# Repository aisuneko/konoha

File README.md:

# Project "konoha"

4-port pure Type-C USB3.0 hub, based on WCH CH634X.

We have:
- All 4 ports in Type-C
- max. approx. USB3.2Gen1 transfer rate (~500MB/s); compatible with USB2.0
- Dedicated charging port
- Adequate ESD protection
- A symmetrical look
- One-sided components for ease of assembly

Name is inspired by Akisato Konoha from *16-bit Sensation*.

## Schematic

Aside from my original idea of forcefully converting the three USB-A downstream ports provided by the CH634X to Type-C, it is largely based on CH634X's reference design with modifications.

Datasheets of the most important chips used in this design could be found under [docs](./docs/).

TL;DR: The USB-A to C conversion is done with TI's HD3SS3220 analog muxes (which appears to be as costly as the CH634X controller itself). CH217 is used for OVC protection while the CH213 diode realize the isolation between 5V and 5VD. ESD protection is realized by the TPD4E02B04 array (USBSS) and USBLC6-2SC6 (USBFS).

## Board

See the board in action:

The board is fabricated using JLCPCB's default JLC04161H-3313 stackup so it should be fairly easy to order your own. Feel free to share any feedback and suggestions on the board design and component routing as I'm also new to high-speed PCB design.

## Caveats

- The board is rather unstable with multiple devices transferring data simultaneously. Certain ports might trigger an occassional hub reset with `disabled by hub (EMI?), re-enabling...` in dmesg.

  Will try to fix in the next revision by improving EMI at the shields of the Type-C connectors, as well as revising the power supply circuit to ensure it's sufficient.

- BOM costs are a bit high; I'll see if I can switch to a cheaper analog mux to reduce costs (and perhaps component count).

## Changelog

- rev1 (2025/11/28): first failed prototype. I can't get it soldered properly in the first place
- rev2 (2026/05/12): Initial working release

## License

As no firmware is involved in this project, it's under `CERN-OHL-S-2.0`.

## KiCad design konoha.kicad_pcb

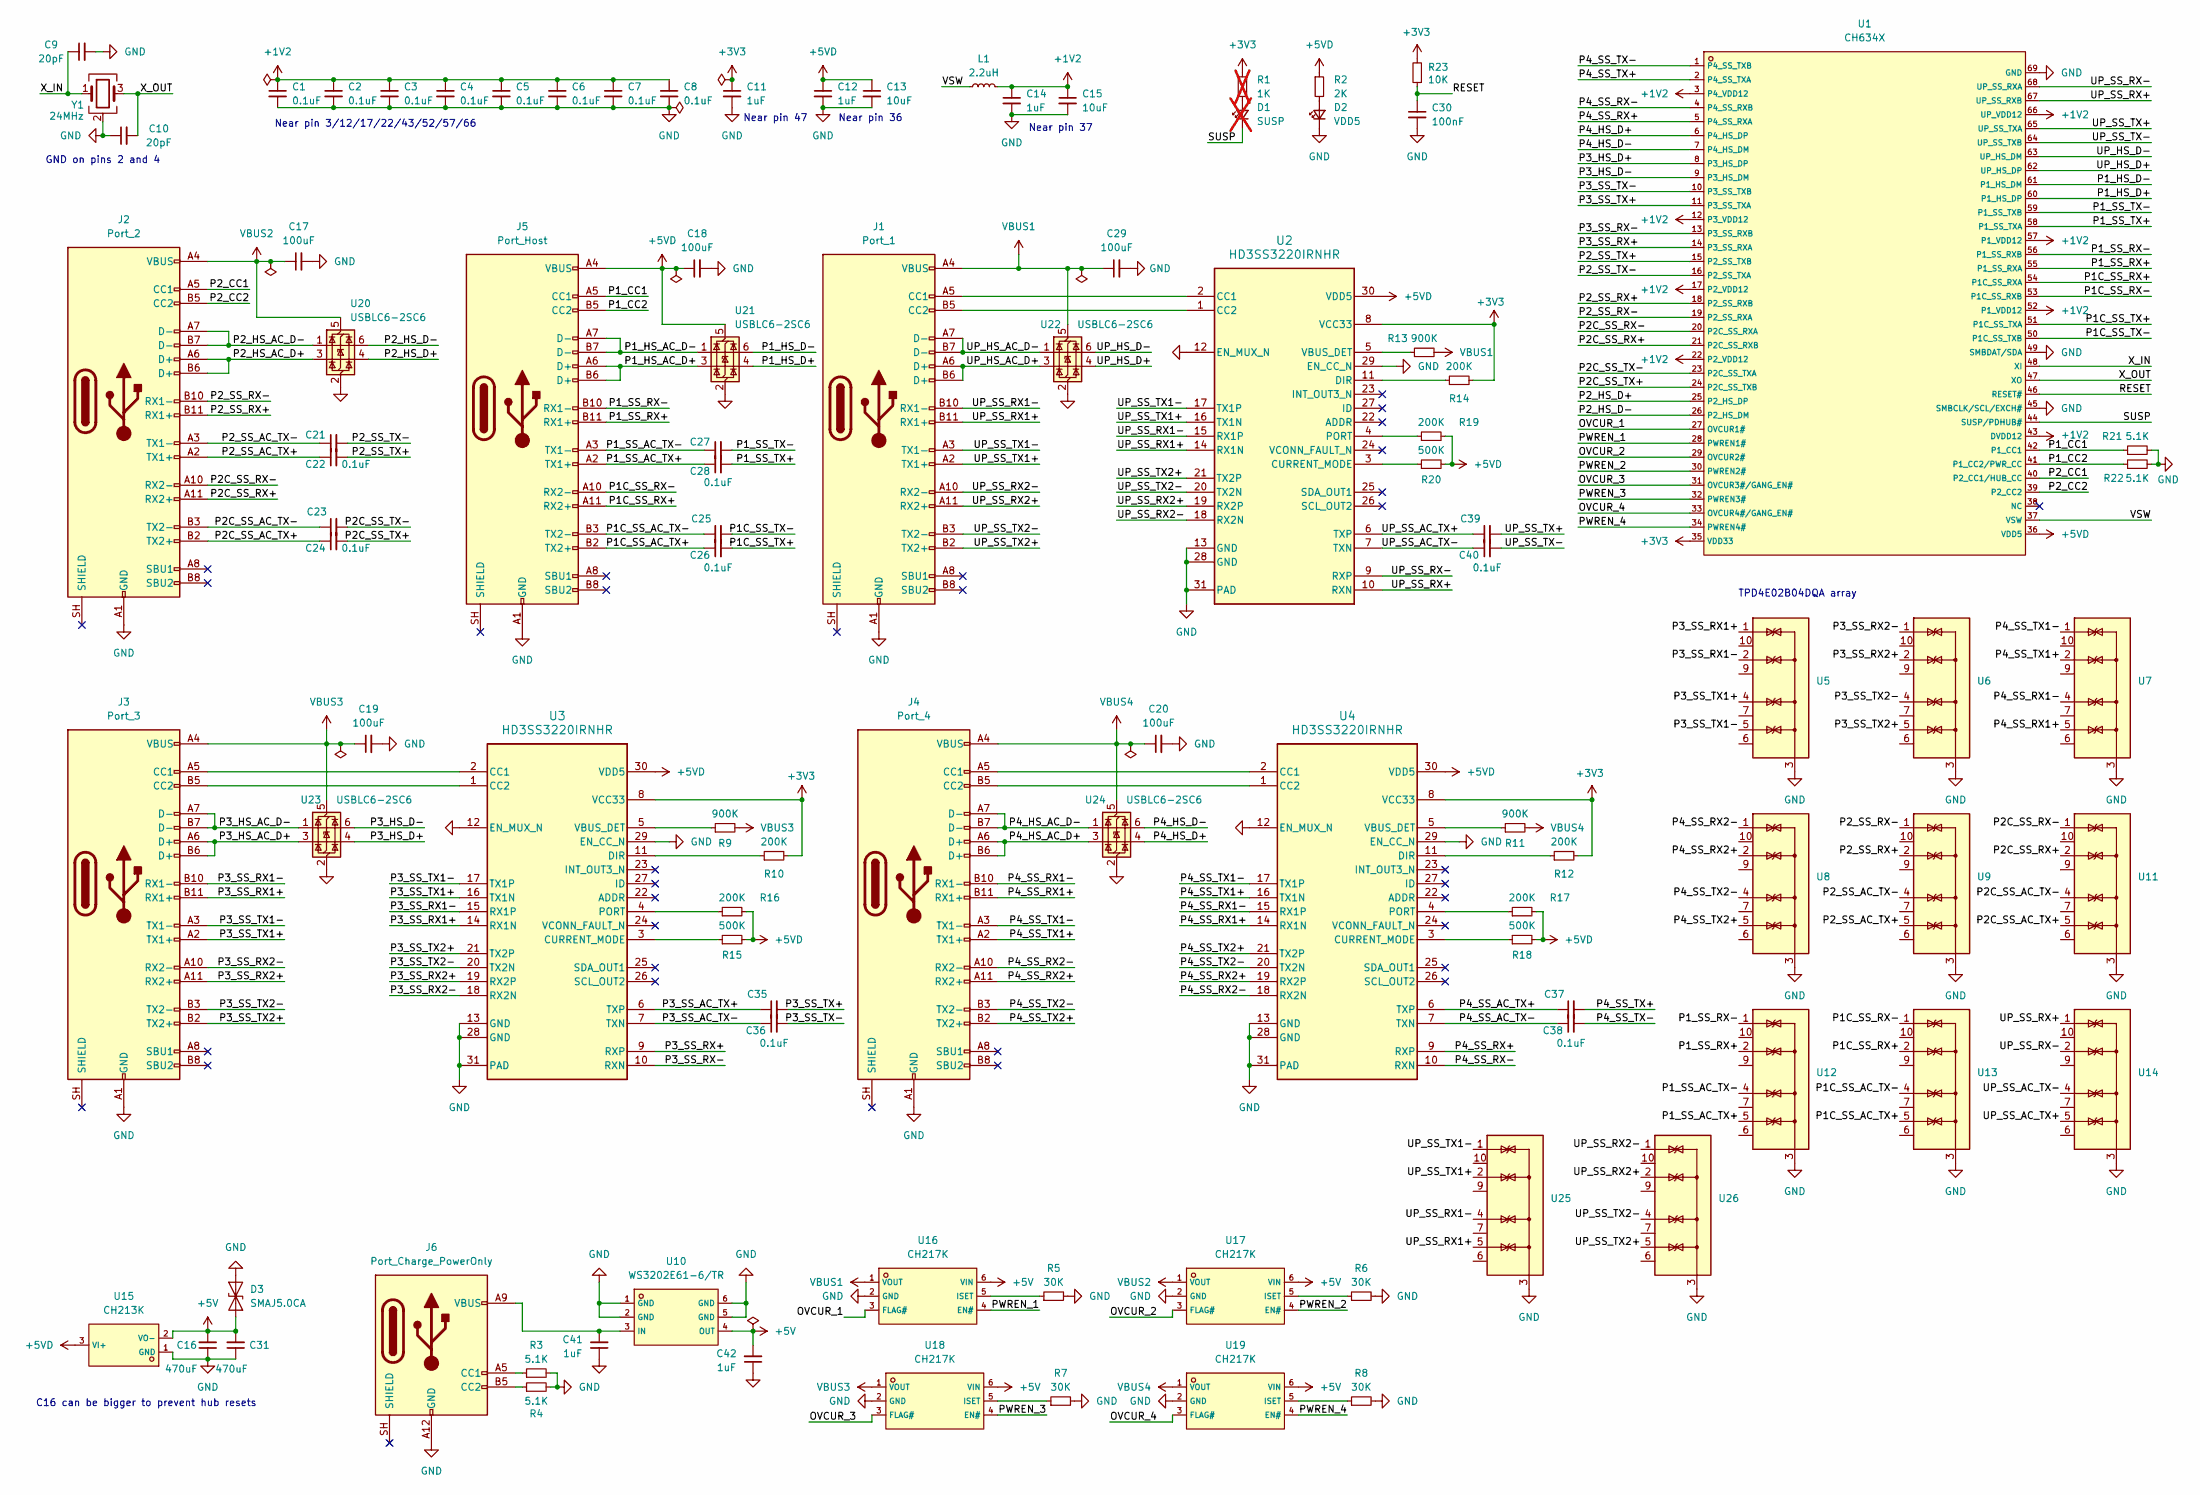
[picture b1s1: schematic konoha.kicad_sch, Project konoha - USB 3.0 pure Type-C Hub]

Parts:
C1, C2, C3, C4, C5, C6, C7, C8, C21, C22, C23, C24, C25, C26, C27, C28, C35, C36, C37, C38, C39, C40: 0.1uF; C_0603_1608Metric_Pad1.08x0.95mm_HandSolder
C9, C10: 20pF; C_0603_1608Metric_Pad1.08x0.95mm_HandSolder
C11, C12, C14, C41, C42: 1uF; C_0603_1608Metric_Pad1.08x0.95mm_HandSolder
C13, C15: 10uF; C_0603_1608Metric_Pad1.08x0.95mm_HandSolder
C16, C31: 470uF; CP_Elec_6.3x7.7
C17, C18, C19, C20, C29: 100uF; C_1206_3216Metric
C30: 100nF; C_0603_1608Metric_Pad1.08x0.95mm_HandSolder
D1: SUSP; LED_0805_2012Metric; not fitted
D2: VDD5; LED_0805_2012Metric
D3: SMAJ5.0CA; D_SMA
J1: Port_1; TYPE-C-USB-SMD_QCHT-143
J2: Port_2; TYPE-C-USB-SMD_QCHT-143
J3: Port_3; TYPE-C-USB-SMD_QCHT-143
J4: Port_4; TYPE-C-USB-SMD_QCHT-143
J5: Port_Host; TYPE-C-USB-SMD_QCHT-143
J6: Port_Charge_PowerOnly; USB_C_Receptacle_HRO_TYPE-C-31-M-17
L1: 2.2uH; L_0805_2012Metric_Pad1.05x1.20mm_HandSolder
R1: 1K; R_0603_1608Metric_Pad0.98x0.95mm_HandSolder; not fitted
R2: 2K; R_0603_1608Metric_Pad0.98x0.95mm_HandSolder
R3, R4, R21, R22: 5.1K; R_0603_1608Metric_Pad0.98x0.95mm_HandSolder
R5, R6, R7, R8: 30K; R_0603_1608Metric_Pad0.98x0.95mm_HandSolder
R9, R11, R13: 900K; R_0603_1608Metric_Pad0.98x0.95mm_HandSolder
R10, R12, R14, R16, R17, R19: 200K; R_0603_1608Metric_Pad0.98x0.95mm_HandSolder
R15, R18, R20: 500K; R_0603_1608Metric_Pad0.98x0.95mm_HandSolder
R23: 10K; R_0603_1608Metric_Pad0.98x0.95mm_HandSolder
U1: CH634X; QFN-68_L8.0-W8.0-P0.40-BL-EP6.2; LCSC C48985831
U2, U3, U4: HD3SS3220IRNHR; Texas_RNH0030A_WQFN-30-1EP_2.5x4.5mm_P0.4mm_EP1.2x3.2mm_The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
U5, U6, U7, U8, U9, U11, U12, U13, U14, U25, U26: TPD4E02B04DQA; USON-10_2.5x1.0mm_P0.5mm
U10: WS3202E61-6/TR; SOT-23-6_L2.9-W1.6-P0.95-LS2.8-BR; LCSC C191359
U15: CH213K; SOT-23-3_L2.9-W1.6-P1.90-LS2.8-BR; LCSC C5456874
U16, U17, U18, U19: CH217K; SOT-23-6_L2.9-W1.6-P0.95-LS2.8-BL; LCSC C7462749
U20, U21, U22, U23, U24: USBLC6-2SC6; SOT-23-6
Y1: 24MHz; Crystal_SMD_2016-4Pin_2.0x1.6mm

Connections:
+1V2: C1.1, C2.1, C3.1, C4.1, C5.1, C6.1, C7.1, C8.1, C14.1, C15.1, L1.2, U1.3 (P4_VDD12), U1.12 (P3_VDD12), U1.17 (P2_VDD12), U1.22 (P2_VDD12), U1.43 (DVDD12), U1.52 (P1_VDD12), U1.57 (P1_VDD12), U1.66 (UP_VDD12)
+3V3: C11.1, R1.1, R10.2, R12.2, R14.2, R23.2, U1.35 (VDD33), U2.8 (VCC33), U3.8 (VCC33), U4.8 (VCC33)
+5V: C16.2, C31.2, C42.2, D3.1 (A1), U10.4 (OUT), U15.2 (VO-), U16.6 (VIN), U17.6 (VIN), U18.6 (VIN), U19.6 (VIN)
+5VD: C12.1, C13.1, C18.1, J5.A4 (VBUS), J5.A9 (VBUS), J5.B4 (VBUS), J5.B9 (VBUS), R2.1, R15.2, R16.2, R17.2, R18.2, R19.2, R20.2, U1.36 (VDD5), U2.30 (VDD5), U3.30 (VDD5), U4.30 (VDD5), U15.3 (VI+), U21.5 (VBUS)
/OVCUR_1: U1.27 (OVCUR1#), U16.3 (FLAG#)
/OVCUR_2: U1.29 (OVCUR2#), U17.3 (FLAG#)
/OVCUR_3: U1.31 (OVCUR3#/GANG_EN#), U18.3 (FLAG#)
/OVCUR_4: U1.33 (OVCUR4#/GANG_EN#), U19.3 (FLAG#)
/P1C_SS_AC_TX+: C26.1, J5.B2 (TX2+), U13.5 (IO4)
/P1C_SS_AC_TX-: C25.1, J5.B3 (TX2-), U13.4 (IO3)
/P1C_SS_RX+: J5.A11 (RX2+), U1.54 (P1C_SS_RXA), U13.2 (IO2)
/P1C_SS_RX-: J5.A10 (RX2-), U1.53 (P1C_SS_RXB), U13.1 (IO1)
/P1C_SS_TX+: C26.2, U1.51 (P1C_SS_TXA)
/P1C_SS_TX-: C25.2, U1.50 (P1C_SS_TXB)
/P1_CC1: J5.A5 (CC1), R21.1, U1.42 (P1_CC1)
/P1_CC2: J5.B5 (CC2), R22.1, U1.41 (P1_CC2/PWR_CC)
/P1_HS_AC_D+: J5.A6 (D+), J5.B6 (D+), U21.3 (I/O2)
/P1_HS_AC_D-: J5.A7 (D-), J5.B7 (D-), U21.1 (I/O1)
/P1_HS_D+: U1.60 (P1_HS_DP), U21.4 (I/O2)
/P1_HS_D-: U1.61 (P1_HS_DM), U21.6 (I/O1)
/P1_SS_AC_TX+: C28.1, J5.A2 (TX1+), U12.5 (IO4)
/P1_SS_AC_TX-: C27.1, J5.A3 (TX1-), U12.4 (IO3)
/P1_SS_RX+: J5.B11 (RX1+), U1.55 (P1_SS_RXA), U12.2 (IO2)
/P1_SS_RX-: J5.B10 (RX1-), U1.56 (P1_SS_RXB), U12.1 (IO1)
/P1_SS_TX+: C28.2, U1.58 (P1_SS_TXA)
/P1_SS_TX-: C27.2, U1.59 (P1_SS_TXB)
/P2C_SS_AC_TX+: C24.1, J2.B2 (TX2+), U11.5 (IO4)
/P2C_SS_AC_TX-: C23.1, J2.B3 (TX2-), U11.4 (IO3)
/P2C_SS_RX+: J2.A11 (RX2+), U1.21 (P2C_SS_RXB), U11.2 (IO2)
/P2C_SS_RX-: J2.A10 (RX2-), U1.20 (P2C_SS_RXA), U11.1 (IO1)
/P2C_SS_TX+: C24.2, U1.24 (P2C_SS_TXB)
/P2C_SS_TX-: C23.2, U1.23 (P2C_SS_TXA)
/P2_CC1: J2.A5 (CC1), U1.40 (P2_CC1/HUB_CC)
/P2_CC2: J2.B5 (CC2), U1.39 (P2_CC2)
/P2_HS_AC_D+: J2.A6 (D+), J2.B6 (D+), U20.3 (I/O2)
/P2_HS_AC_D-: J2.A7 (D-), J2.B7 (D-), U20.1 (I/O1)
/P2_HS_D+: U1.25 (P2_HS_DP), U20.4 (I/O2)
/P2_HS_D-: U1.26 (P2_HS_DM), U20.6 (I/O1)
/P2_SS_AC_TX+: C22.1, J2.A2 (TX1+), U9.5 (IO4)
/P2_SS_AC_TX-: C21.1, J2.A3 (TX1-), U9.4 (IO3)
/P2_SS_RX+: J2.B11 (RX1+), U1.18 (P2_SS_RXB), U9.2 (IO2)
/P2_SS_RX-: J2.B10 (RX1-), U1.19 (P2_SS_RXA), U9.1 (IO1)
/P2_SS_TX+: C22.2, U1.15 (P2_SS_TXB)
/P2_SS_TX-: C21.2, U1.16 (P2_SS_TXA)
/P3_HS_AC_D+: J3.A6 (D+), J3.B6 (D+), U23.3 (I/O2)
/P3_HS_AC_D-: J3.A7 (D-), J3.B7 (D-), U23.1 (I/O1)
/P3_HS_D+: U1.8 (P3_HS_DP), U23.4 (I/O2)
/P3_HS_D-: U1.9 (P3_HS_DM), U23.6 (I/O1)
/P3_SS_AC_TX+: C35.1, U3.6 (TXP)
/P3_SS_AC_TX-: C36.1, U3.7 (TXN)
/P3_SS_RX1+: J3.B11 (RX1+), U3.14 (RX1N), U5.1 (IO1)
/P3_SS_RX1-: J3.B10 (RX1-), U3.15 (RX1P), U5.2 (IO2)
/P3_SS_RX2+: J3.A11 (RX2+), U3.19 (RX2P), U6.2 (IO2)
/P3_SS_RX2-: J3.A10 (RX2-), U3.18 (RX2N), U6.1 (IO1)
/P3_SS_RX+: U1.14 (P3_SS_RXA), U3.9 (RXP)
/P3_SS_RX-: U1.13 (P3_SS_RXB), U3.10 (RXN)
/P3_SS_TX1+: J3.A2 (TX1+), U3.16 (TX1N), U5.4 (IO3)
/P3_SS_TX1-: J3.A3 (TX1-), U3.17 (TX1P), U5.5 (IO4)
/P3_SS_TX2+: J3.B2 (TX2+), U3.21 (TX2P), U6.5 (IO4)
/P3_SS_TX2-: J3.B3 (TX2-), U3.20 (TX2N), U6.4 (IO3)
/P3_SS_TX+: C35.2, U1.11 (P3_SS_TXA)
/P3_SS_TX-: C36.2, U1.10 (P3_SS_TXB)
/P4_HS_AC_D+: J4.A6 (D+), J4.B6 (D+), U24.3 (I/O2)
/P4_HS_AC_D-: J4.A7 (D-), J4.B7 (D-), U24.1 (I/O1)
/P4_HS_D+: U1.6 (P4_HS_DP), U24.4 (I/O2)
/P4_HS_D-: U1.7 (P4_HS_DM), U24.6 (I/O1)
/P4_SS_AC_TX+: C37.1, U4.6 (TXP)
/P4_SS_AC_TX-: C38.1, U4.7 (TXN)
/P4_SS_RX1+: J4.B11 (RX1+), U4.14 (RX1N), U7.5 (IO4)
/P4_SS_RX1-: J4.B10 (RX1-), U4.15 (RX1P), U7.4 (IO3)
/P4_SS_RX2+: J4.A11 (RX2+), U4.19 (RX2P), U8.2 (IO2)
/P4_SS_RX2-: J4.A10 (RX2-), U4.18 (RX2N), U8.1 (IO1)
/P4_SS_RX+: U1.5 (P4_SS_RXA), U4.9 (RXP)
/P4_SS_RX-: U1.4 (P4_SS_RXB), U4.10 (RXN)
/P4_SS_TX1+: J4.A2 (TX1+), U4.16 (TX1N), U7.2 (IO2)
/P4_SS_TX1-: J4.A3 (TX1-), U4.17 (TX1P), U7.1 (IO1)
/P4_SS_TX2+: J4.B2 (TX2+), U4.21 (TX2P), U8.5 (IO4)
/P4_SS_TX2-: J4.B3 (TX2-), U4.20 (TX2N), U8.4 (IO3)
/P4_SS_TX+: C37.2, U1.2 (P4_SS_TXA)
/P4_SS_TX-: C38.2, U1.1 (P4_SS_TXB)
/PWREN_1: U1.28 (PWREN1#), U16.4 (EN#)
/PWREN_2: U1.30 (PWREN2#), U17.4 (EN#)
/PWREN_3: U1.32 (PWREN3#), U18.4 (EN#)
/PWREN_4: U1.34 (PWREN4#), U19.4 (EN#)
/RESET: C30.1, R23.1, U1.46 (RESET#)
/SUSP: D1.1 (K), U1.44 (SUSP/PDHUB#)
/UP_HS_AC_D+: J1.A6 (D+), J1.B6 (D+), U22.3 (I/O2)
/UP_HS_AC_D-: J1.A7 (D-), J1.B7 (D-), U22.1 (I/O1)
/UP_HS_D+: U1.62 (UP_HS_DP), U22.4 (I/O2)
/UP_HS_D-: U1.63 (UP_HS_DM), U22.6 (I/O1)
/UP_SS_AC_TX+: C39.1, U2.6 (TXP), U14.5 (IO4)
/UP_SS_AC_TX-: C40.1, U2.7 (TXN), U14.4 (IO3)
/UP_SS_RX1+: J1.B11 (RX1+), U2.14 (RX1N), U25.5 (IO4)
/UP_SS_RX1-: J1.B10 (RX1-), U2.15 (RX1P), U25.4 (IO3)
/UP_SS_RX2+: J1.A11 (RX2+), U2.19 (RX2P), U26.2 (IO2)
/UP_SS_RX2-: J1.A10 (RX2-), U2.18 (RX2N), U26.1 (IO1)
/UP_SS_RX+: U1.67 (UP_SS_RXB), U2.10 (RXN), U14.1 (IO1)
/UP_SS_RX-: U1.68 (UP_SS_RXA), U2.9 (RXP), U14.2 (IO2)
/UP_SS_TX1+: J1.A2 (TX1+), U2.16 (TX1N), U25.2 (IO2)
/UP_SS_TX1-: J1.A3 (TX1-), U2.17 (TX1P), U25.1 (IO1)
/UP_SS_TX2+: J1.B2 (TX2+), U2.21 (TX2P), U26.5 (IO4)
/UP_SS_TX2-: J1.B3 (TX2-), U2.20 (TX2N), U26.4 (IO3)
/UP_SS_TX+: C39.2, U1.65 (UP_SS_TXA)
/UP_SS_TX-: C40.2, U1.64 (UP_SS_TXB)
/VSW: L1.1, U1.37 (VSW)
/X_IN: C9.1, U1.48 (XI), Y1.1
/X_OUT: C10.2, U1.47 (XO), Y1.3
GND: C1.2, C2.2, C3.2, C4.2, C5.2, C6.2, C7.2, C8.2, C9.2, C10.1, C11.2, C12.2, C13.2, C14.2, C15.2, C16.1, C17.2, C18.2, C19.2, C20.2, C29.2, C30.2, C31.1, C41.1, C42.1, D2.1 (K), D3.2 (A2), J1.A1 (GND), J1.A12 (GND), J1.B1 (GND), J1.B12 (GND), J2.A1 (GND), J2.A12 (GND), J2.B1 (GND), J2.B12 (GND), J3.A1 (GND), J3.A12 (GND), J3.B1 (GND), J3.B12 (GND), J4.A1 (GND), J4.A12 (GND), J4.B1 (GND), J4.B12 (GND), J5.A1 (GND), J5.A12 (GND), J5.B1 (GND), J5.B12 (GND), J6.A12 (GND), J6.B12 (GND), R3.2, R4.2, R5.2, R6.2, R7.2, R8.2, R21.2, R22.2, U1.45 (SMBCLK/SCL/EXCH#), U1.49 (SMBDAT/SDA), U1.69 (GND), U2.12 (EN_MUX_N), U2.13 (GND), U2.28 (GND), U2.29 (EN_CC_N), U2.31 (PAD), U3.12 (EN_MUX_N), U3.13 (GND), U3.28 (GND), U3.29 (EN_CC_N), U3.31 (PAD), U4.12 (EN_MUX_N), U4.13 (GND), U4.28 (GND), U4.29 (EN_CC_N), U4.31 (PAD), U5.3 (G), U5.8 (G), U6.3 (G), U6.8 (G), U7.3 (G), U7.8 (G), U8.3 (G), U8.8 (G), U9.3 (G), U9.8 (G), U10.1 (GND), U10.2 (GND), U10.5 (GND), U10.6 (GND), U11.3 (G), U11.8 (G), U12.3 (G), U12.8 (G), U13.3 (G), U13.8 (G), U14.3 (G), U14.8 (G), U15.1 (GND), U16.2 (GND), U17.2 (GND), U18.2 (GND), U19.2 (GND), U20.2 (GND), U21.2 (GND), U22.2 (GND), U23.2 (GND), U24.2 (GND), U25.3 (G), U25.8 (G), U26.3 (G), U26.8 (G), Y1.2 (G), Y1.4 (G)
unnamed: D1.2 (A), R1.2
unnamed: D2.2 (A), R2.2
unnamed: J1.A5 (CC1), U2.2 (CC1)
unnamed: J1.B5 (CC2), U2.1 (CC2)
unnamed: J3.A5 (CC1), U3.2 (CC1)
unnamed: J3.B5 (CC2), U3.1 (CC2)
unnamed: J4.A5 (CC1), U4.2 (CC1)
unnamed: J4.B5 (CC2), U4.1 (CC2)
unnamed: J6.A5 (CC1), R3.1
unnamed: J6.B5 (CC2), R4.1
unnamed: R20.1, U2.3 (CURRENT_MODE)
unnamed: R14.1, U2.11 (DIR)
unnamed: R19.1, U2.4 (PORT)
unnamed: R13.1, U2.5 (VBUS_DET)
unnamed: R15.1, U3.3 (CURRENT_MODE)
unnamed: R10.1, U3.11 (DIR)
unnamed: R16.1, U3.4 (PORT)
unnamed: R9.1, U3.5 (VBUS_DET)
unnamed: R18.1, U4.3 (CURRENT_MODE)
unnamed: R12.1, U4.11 (DIR)
unnamed: R17.1, U4.4 (PORT)
unnamed: R11.1, U4.5 (VBUS_DET)
unnamed: C41.2, J6.A9 (VBUS), J6.B9 (VBUS), U10.3 (IN)
unnamed: R5.1, U16.5 (ISET)
unnamed: R6.1, U17.5 (ISET)
unnamed: R7.1, U18.5 (ISET)
unnamed: R8.1, U19.5 (ISET)
VBUS1: C29.1, J1.A4 (VBUS), J1.A9 (VBUS), J1.B4 (VBUS), J1.B9 (VBUS), R13.2, U16.1 (VOUT), U22.5 (VBUS)
VBUS2: C17.1, J2.A4 (VBUS), J2.A9 (VBUS), J2.B4 (VBUS), J2.B9 (VBUS), U17.1 (VOUT), U20.5 (VBUS)
VBUS3: C19.1, J3.A4 (VBUS), J3.A9 (VBUS), J3.B4 (VBUS), J3.B9 (VBUS), R9.2, U18.1 (VOUT), U23.5 (VBUS)
VBUS4: C20.1, J4.A4 (VBUS), J4.A9 (VBUS), J4.B4 (VBUS), J4.B9 (VBUS), R11.2, U19.1 (VOUT), U24.5 (VBUS)

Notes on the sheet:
Near pin 47
Near pin 36
Near pin 37
TPD4E02B04DQA array
Near pin 3/12/17/22/43/52/57/66
C16 can be bigger to prevent hub resets
GND on pins 2 and 4

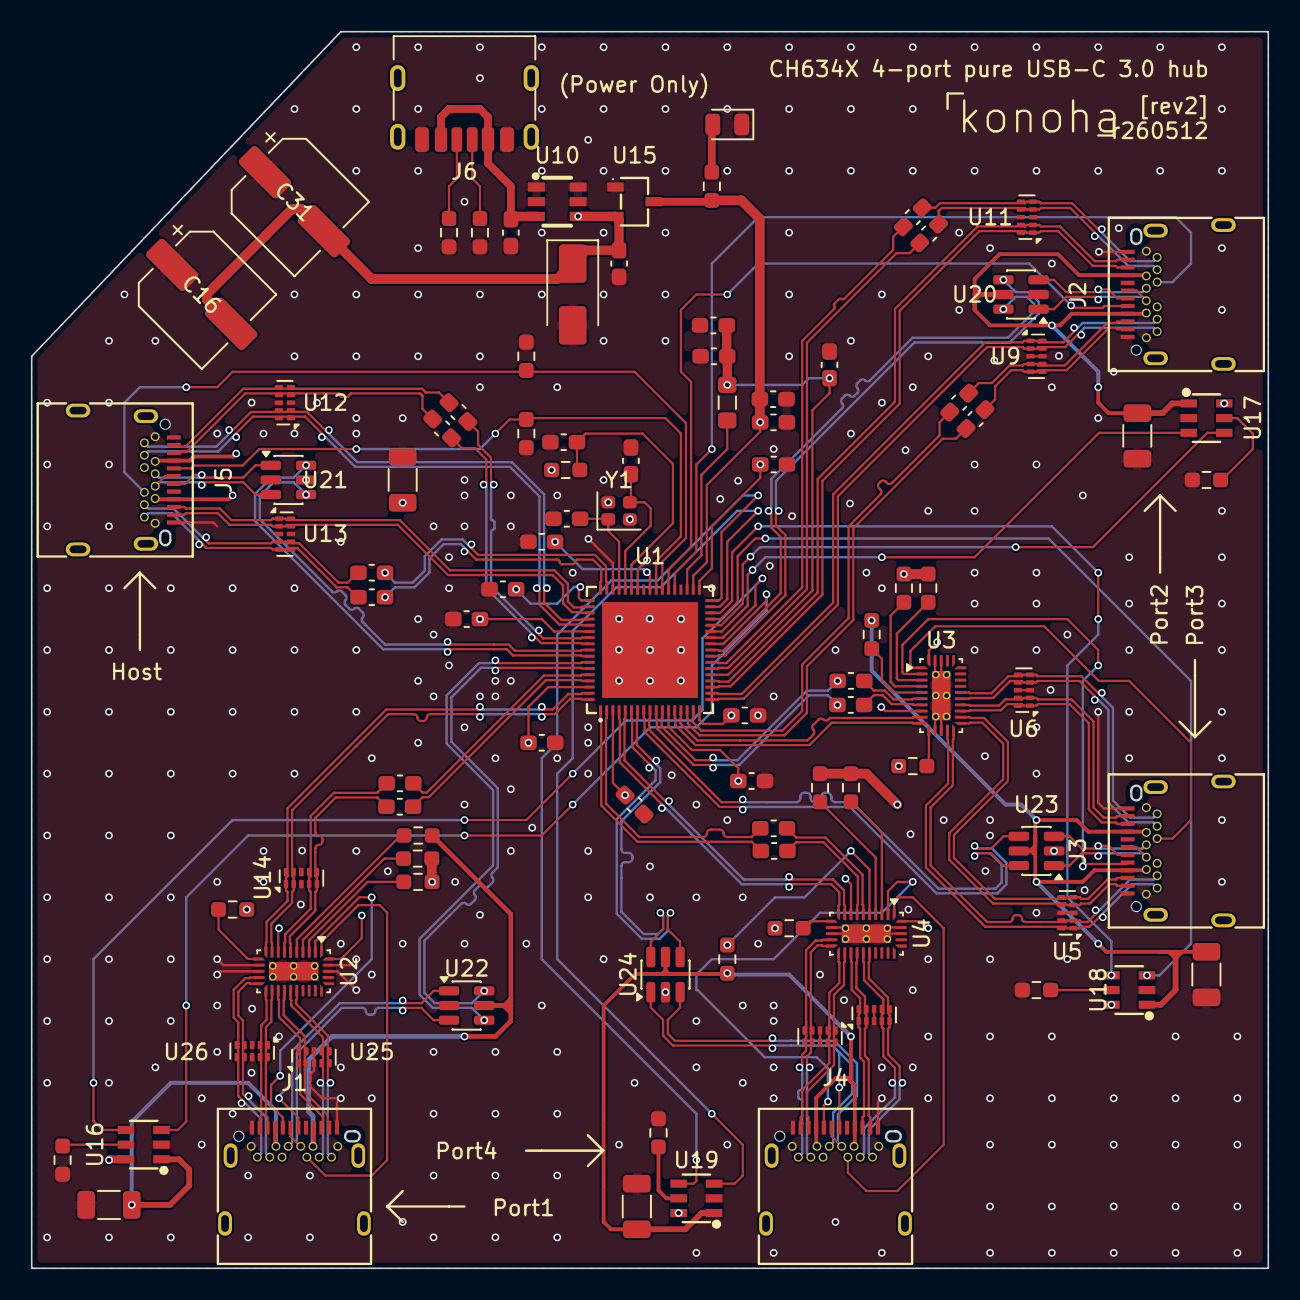
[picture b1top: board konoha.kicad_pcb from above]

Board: 4 copper layers, 80.0 x 80.0 mm, 97 parts (0 on the bottom side), 137 nets.

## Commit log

2026-05-13 datasheets
2026-05-13 update symbols and footprints
2026-05-13 v2 schematic and board
2026-05-27 fix invalid rescue layer
2026-05-27 update assets
2026-05-27 add Readme
